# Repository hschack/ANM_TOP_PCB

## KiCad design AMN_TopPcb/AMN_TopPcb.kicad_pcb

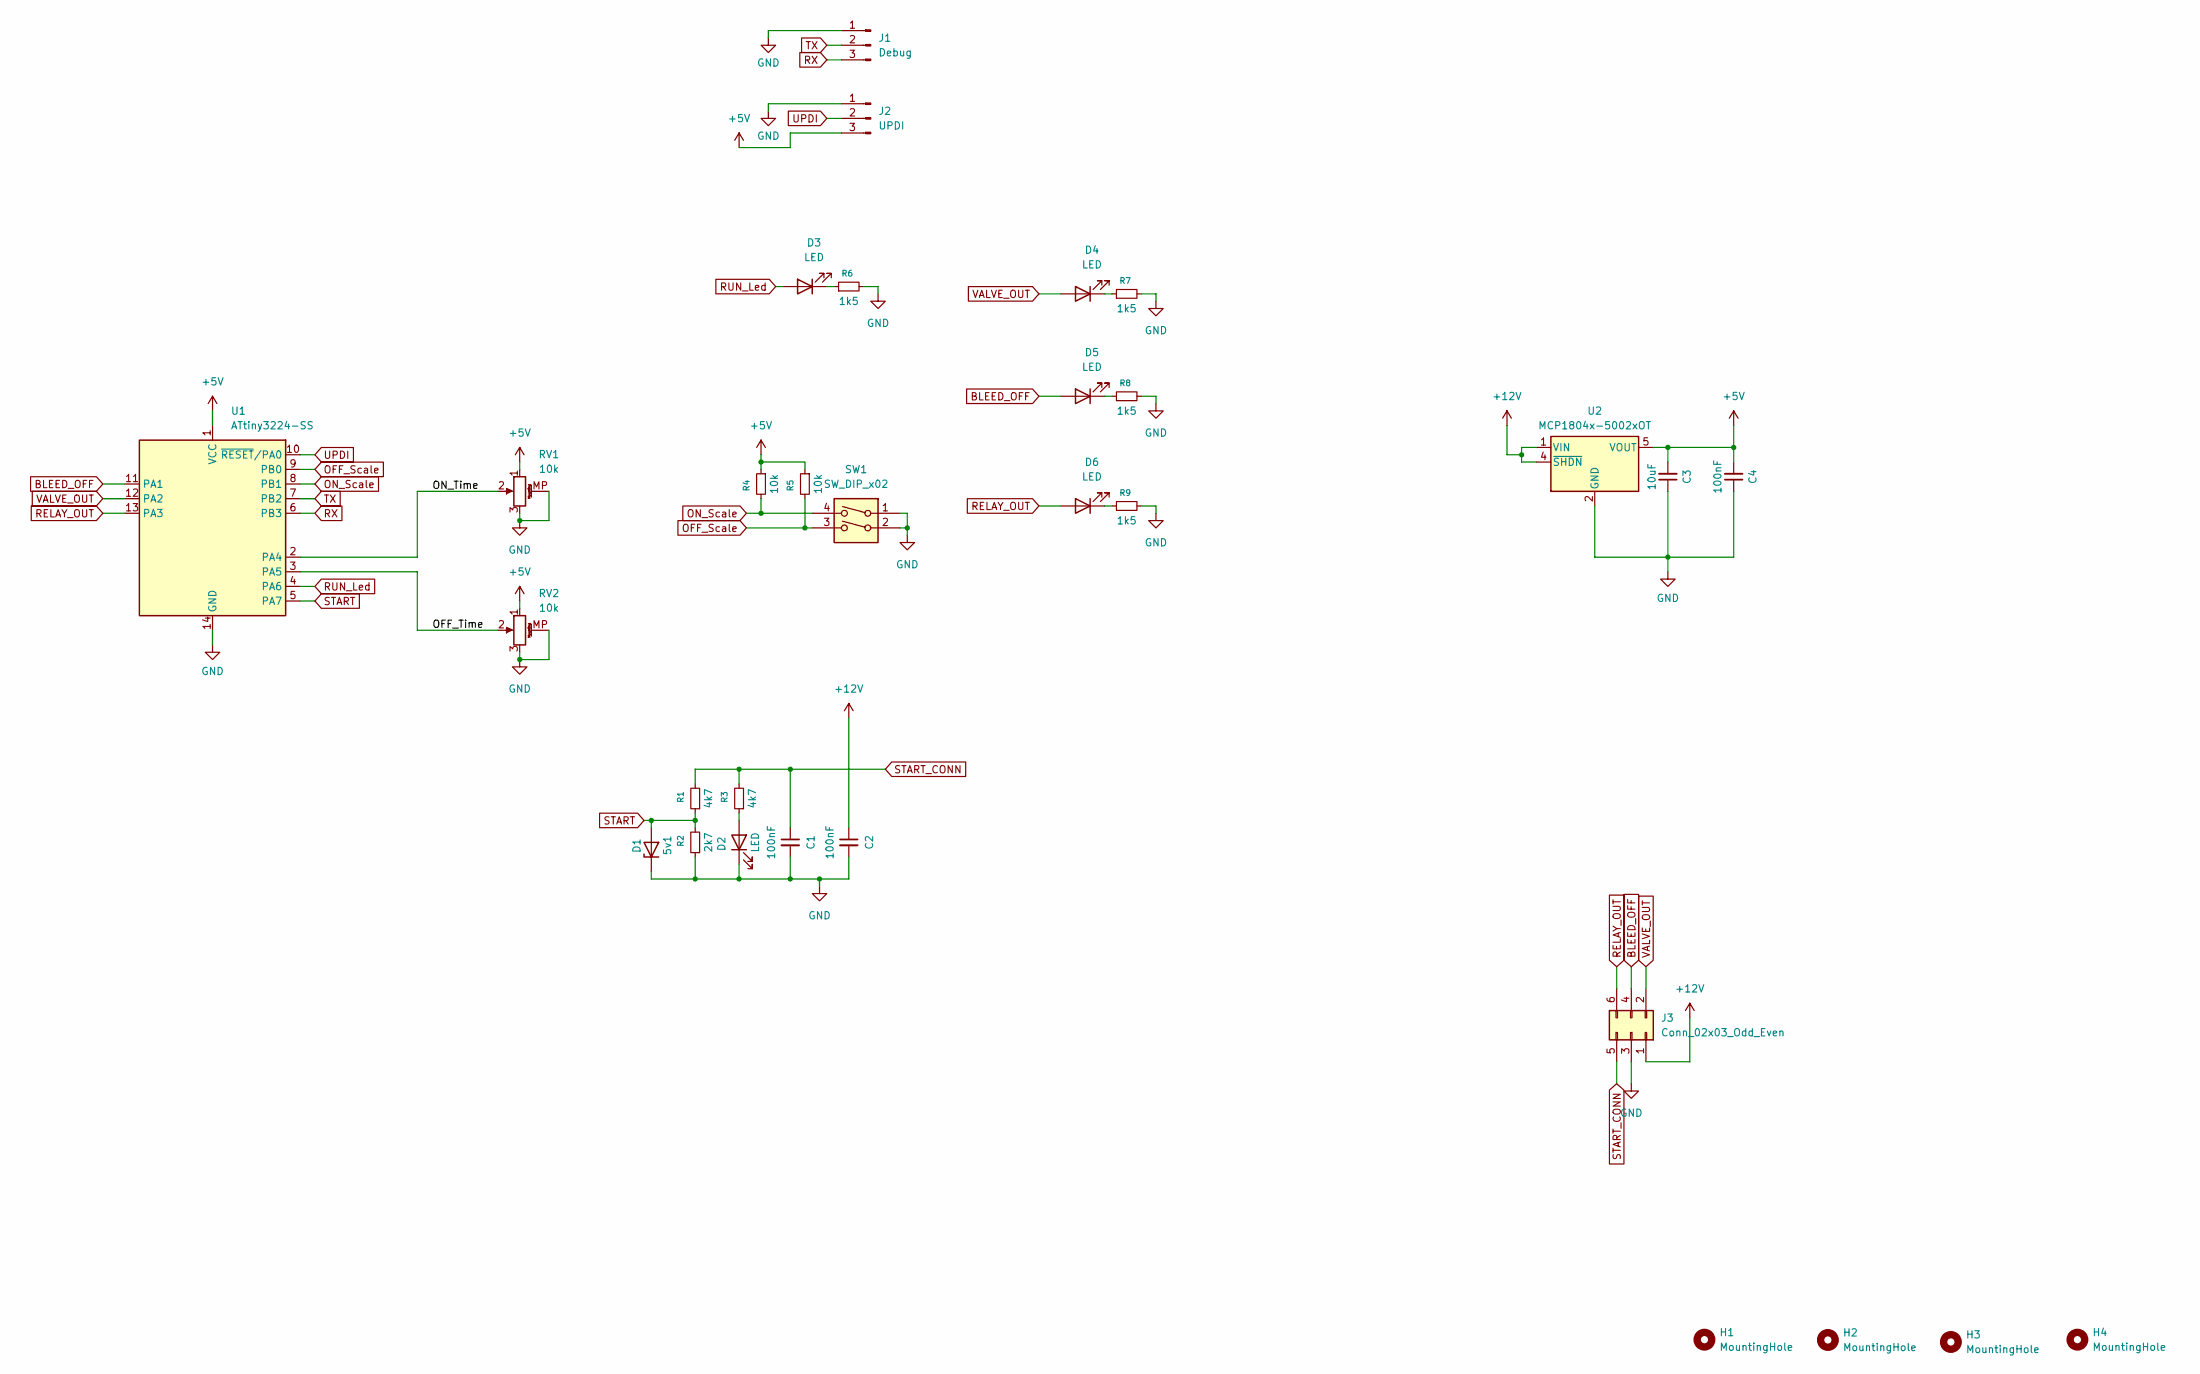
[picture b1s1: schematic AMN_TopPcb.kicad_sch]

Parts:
C1, C2, C4: 100nF; C_0603_1608Metric
C3: 10uF; C_0603_1608Metric
D1: 5v1; D_SMF
D2, D3, D4, D5, D6: LED; LED_0805_2012Metric
H1, H2, H3, H4: MountingHole; MountingHole_3.5mm
J1: Debug; PinHeader_1x03_P2.54mm_Vertical
J2: UPDI; PinHeader_1x03_P2.54mm_Vertical
J3: Conn_02x03_Odd_Even; PinHeader_2x03_P2.54mm_Vertical
R1, R3: 4k7; R_0603_1608Metric
R2: 2k7; R_0603_1608Metric
R4, R5: 10k; R_0603_1608Metric
R6, R7, R8, R9: 1k5; R_0603_1608Metric
RV1, RV2: 10k; Potentiometer_Alps_RK09K_Single_Vertical
SW1: SW_DIP_x02; SW_DIP_SPSTx02_Slide_9.78x7.26mm_W7.62mm_P2.54mm
U1: ATtiny3224-SS; SOIC-14_3.9x8.7mm_P1.27mm
U2: MCP1804x-5002xOT; SOT-23-5

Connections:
+5V: C3.2, C4.2, J2.3, R4.1, R5.1, RV1.1, RV2.1, U1.1 (VCC), U2.5 (VOUT)
+12V: C2.1, J3.1, U2.1 (VIN), U2.4 (~SHDN)
/OFF_Time: RV2.2, U1.3 (PA5)
/ON_Time: RV1.2, U1.2 (PA4)
BLEED_OFF: D5.2 (A), J3.4, U1.11 (PA1)
GND: C1.2, C2.2, C3.1, C4.1, D1.1 (K), D2.1 (K), J1.1, J2.1, J3.3, R2.1, R6.2, R7.2, R8.2, R9.2, RV1.3, RV1.MP (MountPin), RV2.3, RV2.MP (MountPin), SW1.1, SW1.2, U1.14 (GND), U2.2 (GND)
unnamed: D2.2 (A), R3.1
unnamed: D3.1 (K), R6.1
unnamed: D4.1 (K), R7.1
unnamed: D5.1 (K), R8.1
unnamed: D6.1 (K), R9.1
OFF_Scale: R5.2, SW1.3, U1.9 (PB0)
ON_Scale: R4.2, SW1.4, U1.8 (PB1)
RELAY_OUT: D6.2 (A), J3.6, U1.13 (PA3)
RUN_Led: D3.2 (A), U1.4 (PA6)
RX: J1.3, U1.6 (PB3)
START: D1.2 (A), R1.1, R2.2, U1.5 (PA7)
START_CONN: C1.1, J3.5, R1.2, R3.2
TX: J1.2, U1.7 (PB2)
UPDI: J2.2, U1.10 (~RESET/PA0)
VALVE_OUT: D4.2 (A), J3.2, U1.12 (PA2)

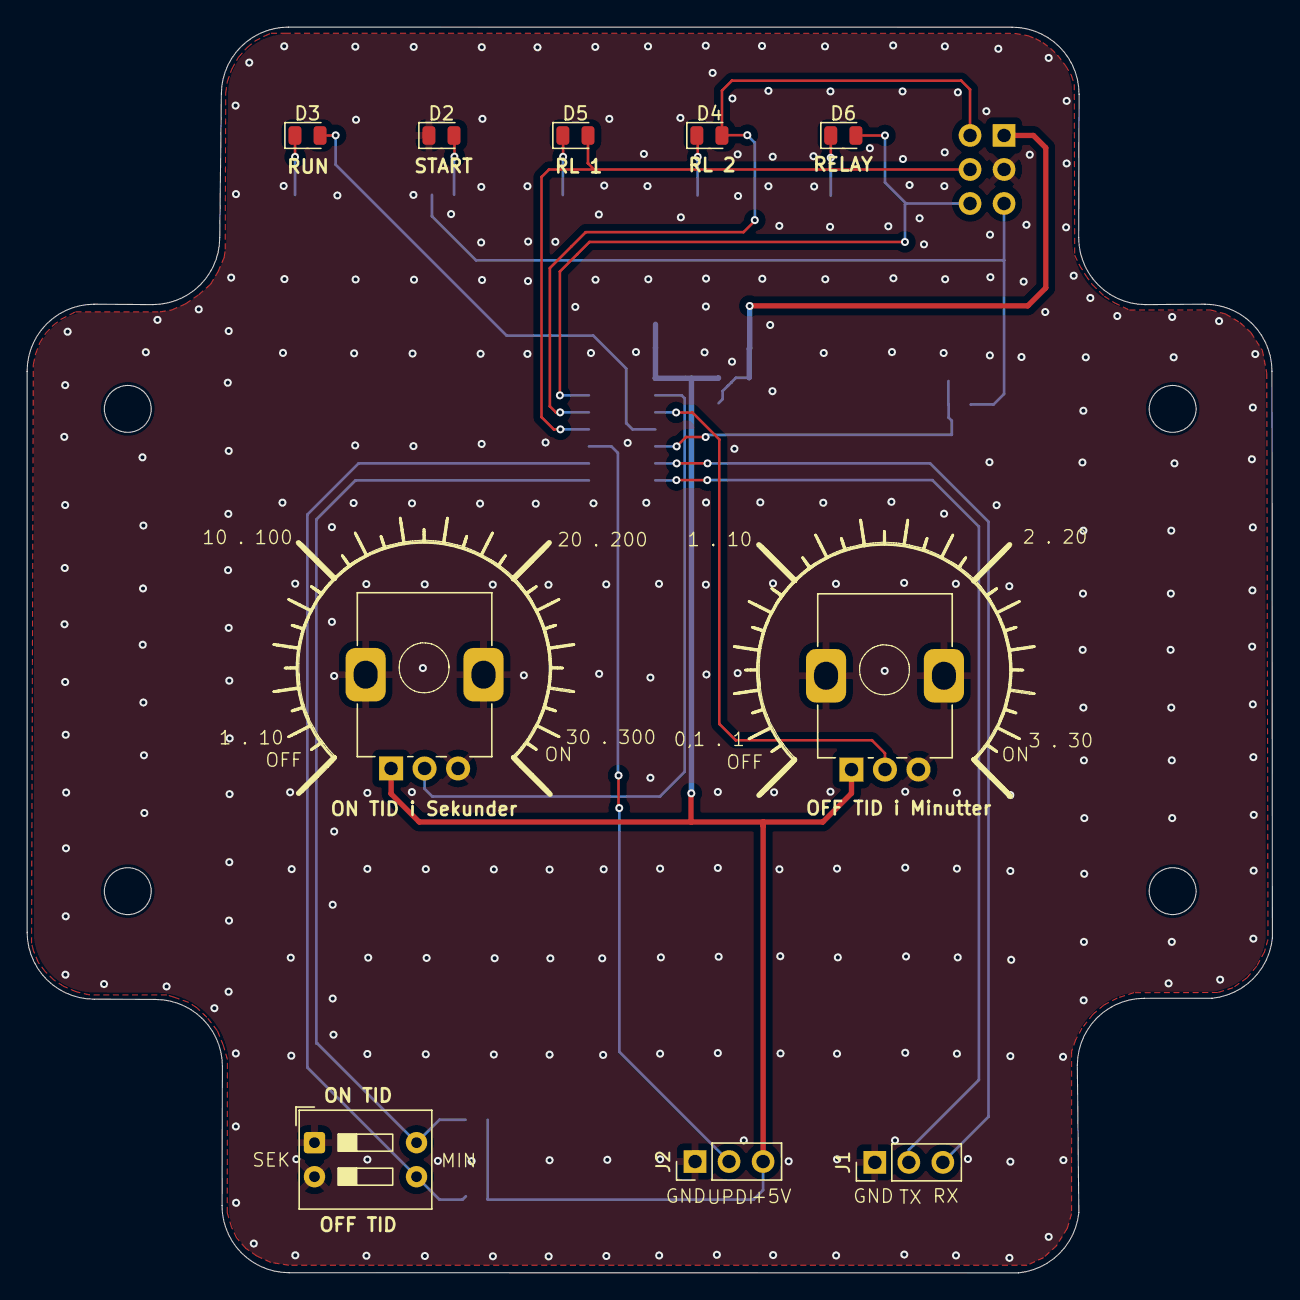
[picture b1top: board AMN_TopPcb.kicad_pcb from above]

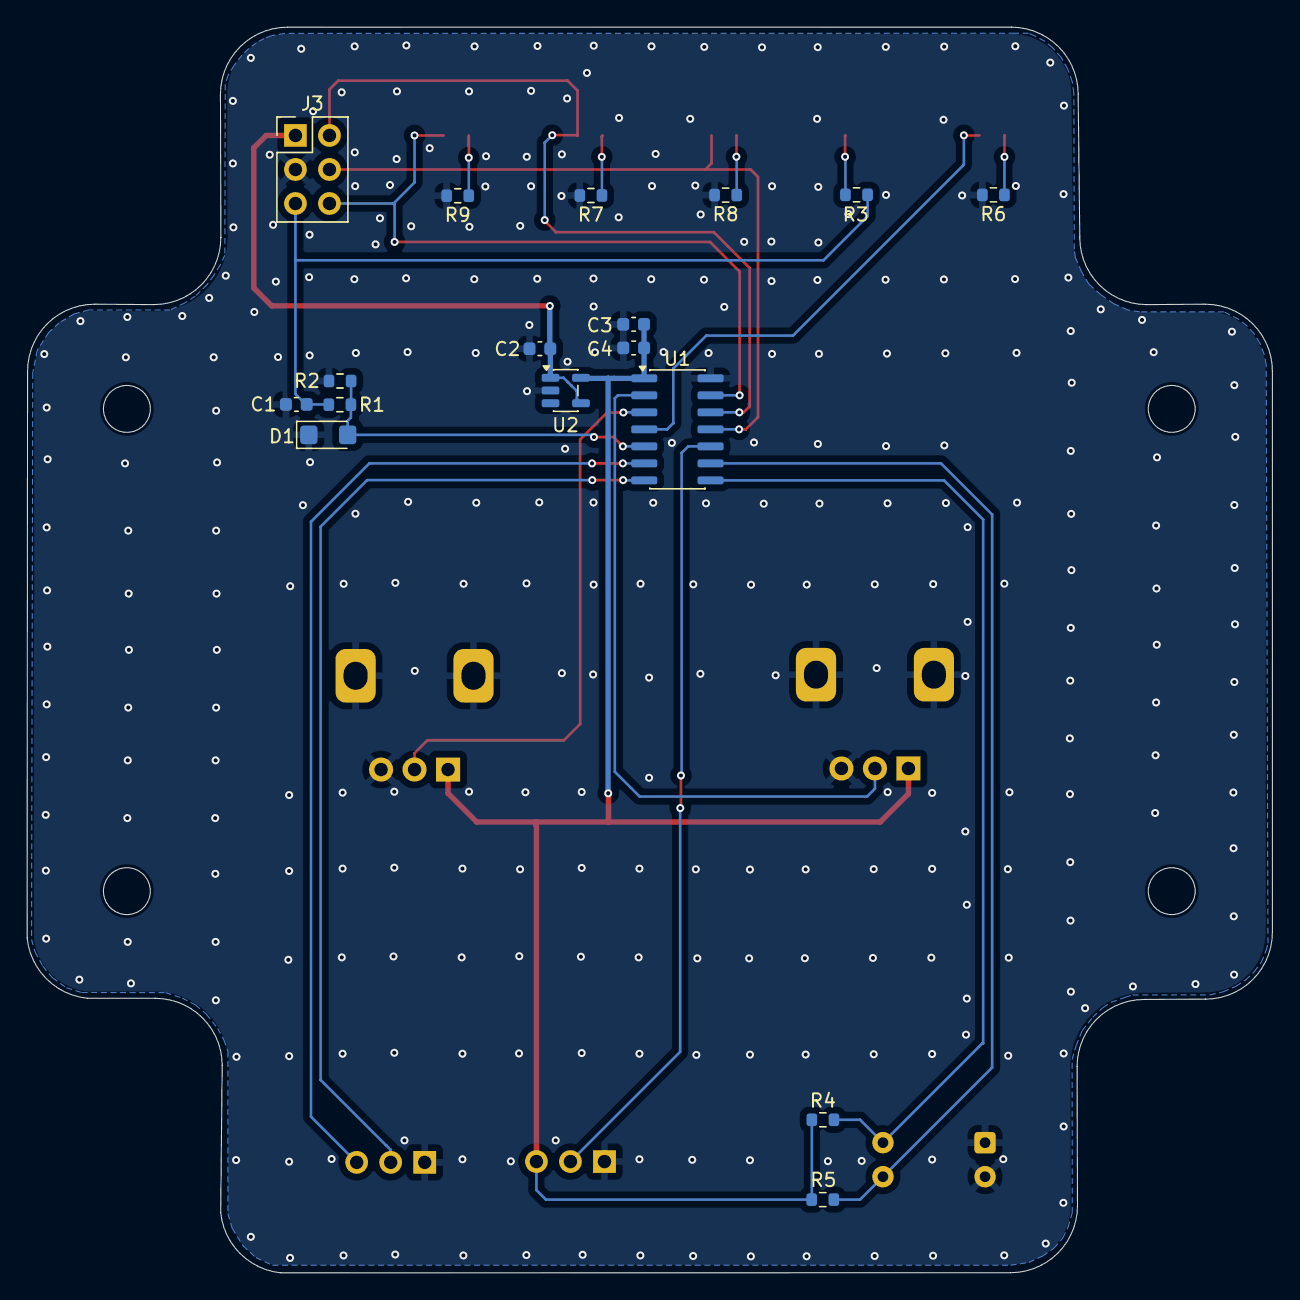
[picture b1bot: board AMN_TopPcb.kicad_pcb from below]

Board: 2 copper layers, 93.0 x 93.0 mm, 31 parts (17 on the bottom side), 21 nets.
